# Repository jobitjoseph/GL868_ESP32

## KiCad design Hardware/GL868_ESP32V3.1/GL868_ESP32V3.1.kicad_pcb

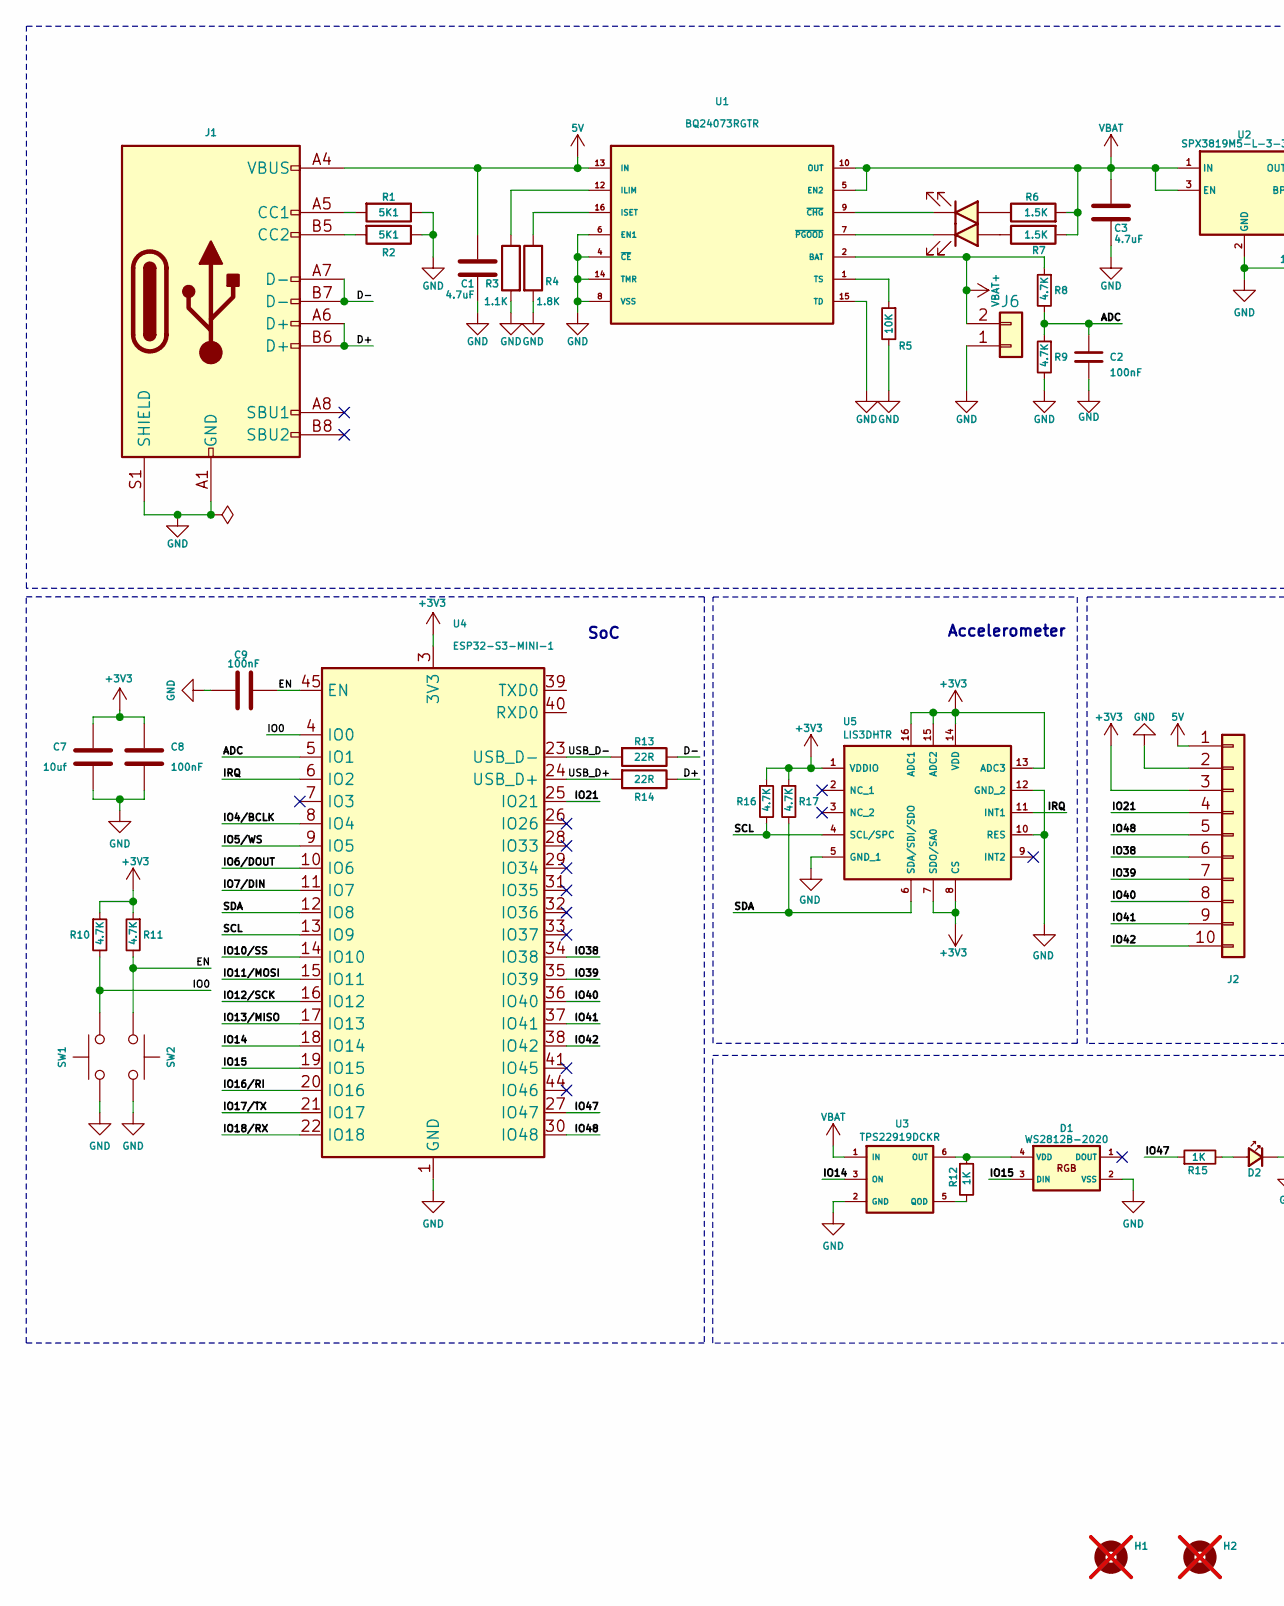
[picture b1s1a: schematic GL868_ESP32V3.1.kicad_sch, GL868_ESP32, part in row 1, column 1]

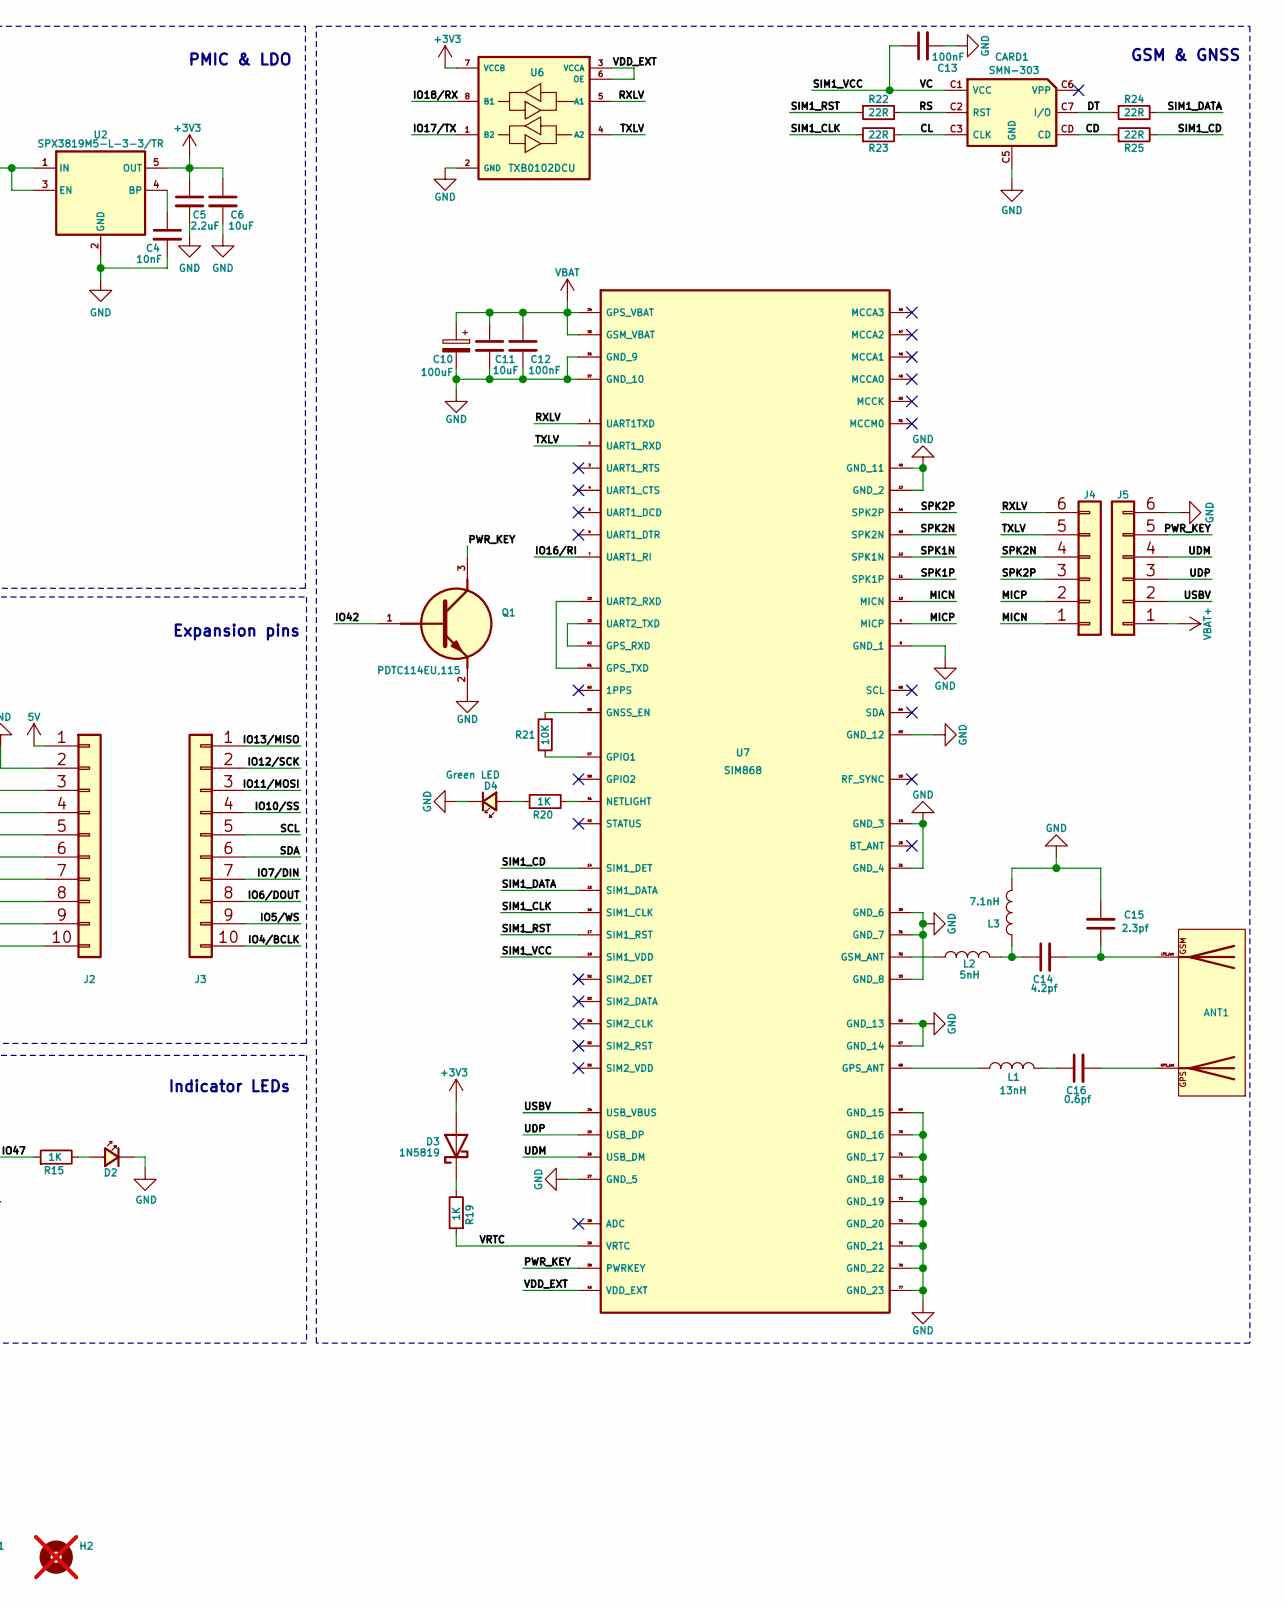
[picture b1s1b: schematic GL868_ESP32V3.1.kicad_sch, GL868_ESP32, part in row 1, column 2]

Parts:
ANT1: ANT; GL868_Combo_ANT
C1, C3: 4.7uF; C_0402_1005Metric; LCSC Part # C23733
C2, C8, C9, C12, C13: 100nF; C_0402_1005Metric; LCSC Part # C307331
C4: 10nF; C_0402_1005Metric; LCSC Part # C15195
C5: 2.2uF; C_0402_1005Metric; LCSC Part # C12530
C6, C11: 10uF; C_0402_1005Metric; LCSC Part # C15525
C7: 10uf; C_0402_1005Metric; LCSC Part # C15525
C10: 100uF; CP_EIA-3528-15_AVX-H; LCSC Part # C16133
C14: 4.2pf; C_0402_1005Metric; LCSC Part # C1855356
C15: 2.3pf; C_0402_1005Metric; LCSC Part # C2190124
C16: 0.6pf; C_0402_1005Metric; LCSC Part # C426333
CARD1: SMN-303; SIM-SMD_SMN-303; Manufacturer Part SMN-303; LCSC Part # C266888
D1: WS2812B-2020; LED_WS2812B-2020_PLCC4_2.0x2.0mm; LCSC Part # C5349955
D2, D4: Green LED; LED_0603_1608Metric; LCSC Part # C965804
D3: 1N5819; D_SOD-523; LCSC Part # C5185918
H1, H2: MountingHole; MountingHole_2.2mm_M2_DIN965; not fitted
J1: USB_C_Receptacle_USB2.0; USB_C_Receptacle_HRO_TYPE-C-31-M-12; LCSC Part # C2765186
J2, J3: Conn_01x10; PinHeader_1x10_P2.54mm_Vertical
J4, J5: Conn_01x06; PinHeader_1x06_P2.54mm_Vertical
J6: Conn_01x02; CONN-SMD_2P-P2.50_HCTL_HC-XH-2ALT; LCSC Part # C7429680
L1: 13nH; L_0402_1005Metric; LCSC Part # C2991840
L2: 5nH; L_0402_1005Metric
L3: 7.1nH; L_0402_1005Metric
LED1: Red LED; LED_0603_1608Metric; LCSC Part # C2286
LED2: Blue LED; LED_0603_1608Metric; LCSC Part # C965807
Q1: PDTC114EU,115; PDTC114EU115; LCSC Part # C135830
R1, R2: 5K1; R_0402_1005Metric; LCSC Part # C25905
R3: 1.1K; R_0402_1005Metric; LCSC Part # C174195
R4: 1.8K; R_0402_1005Metric; LCSC Part # C25867
R5, R21: 10K; R_0402_1005Metric; LCSC Part # C25744
R6, R7: 1.5K; R_0402_1005Metric; LCSC Part # C25867
R8, R9, R10, R11, R16, R17: 4.7K; R_0402_1005Metric; LCSC Part # C25900
R12, R15, R19, R20: 1K; R_0402_1005Metric; LCSC Part # C11702
R13, R14, R22, R23, R24, R25: 22R; R_0402_1005Metric; LCSC Part # C25092
SW1, SW2: SW_Push; Tactile 3x4x2mm TS-A010; LCSC Part # C720477
U1: BQ24073RGTR; IC_BQ24072RGTR; LCSC Part # C15220
U2: SPX3819M5-L-3-3/TR; SOT-23-5; LCSC Part # C9055
U3: TPS22919DCKR; SOT65P210X110-6N; LCSC Part # C2149796
U4: ESP32-S3-MINI-1; ESP32-S2-MINI-1; LCSC Part # C3013941
U5: LIS3DHTR; LCSC Part # C15134
U6: TXB0102DCU; VSSOP-8_2.3x2mm_P0.5mm; LCSC Part # C60709
U7: SIM868; LCSC Part # C39162023

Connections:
5V: C1.1, J1.A4 (VBUS), J1.A9 (VBUS), J1.B4 (VBUS), J1.B9 (VBUS), J2.1, U1.13 (IN)
+3V3: C5.1, C6.1, C7.1, C8.1, D3.2 (A), J2.3, R10.1, R11.1, R16.1, R17.1, U2.5 (OUT), U4.3 (3V3), U5.1 (VDDIO), U5.7 (SDO/SA0), U5.8 (CS), U5.13 (ADC3), U5.14 (VDD), U5.15 (ADC2), U5.16 (ADC1), U6.7 (VCCB)
/ADC: C2.1, R8.2, R9.1, U4.5 (IO1)
/CD: CARD1.CD, R25.1
/CL: CARD1.C3 (CLK), R23.2
/D+: J1.A6 (D+), J1.B6 (D+), R14.1
/D-: J1.A7 (D-), J1.B7 (D-), R13.1
/DT: CARD1.C7 (I/O), R24.1
/EN: C9.1, R11.2, SW2.1, U4.45 (EN)
/IO0: R10.2, SW1.2, U4.4 (IO0)
/IO4/BCLK: J3.10, U4.8 (IO4)
/IO5/WS: J3.9, U4.9 (IO5)
/IO6/DOUT: J3.8, U4.10 (IO6)
/IO7/DIN: J3.7, U4.11 (IO7)
/IO10/SS: J3.4, U4.14 (IO10)
/IO11/MOSI: J3.3, U4.15 (IO11)
/IO12/SCK: J3.2, U4.16 (IO12)
/IO13/MISO: J3.1, U4.17 (IO13)
/IO14: U3.3 (ON), U4.18 (IO14)
/IO15: D1.3 (DIN), U4.19 (IO15)
/IO16/RI: U4.20 (IO16), U7.7 (UART1_RI)
/IO17/TX: U4.21 (IO17), U6.1 (B2)
/IO18/RX: U4.22 (IO18), U6.8 (B1)
/IO21: J2.4, U4.25 (IO21)
/IO38: J2.6, U4.34 (IO38)
/IO39: J2.7, U4.35 (IO39)
/IO40: J2.8, U4.36 (IO40)
/IO41: J2.9, U4.37 (IO41)
/IO42: J2.10, Q1.1 (B), U4.38 (IO42)
/IO47: R15.1, U4.27 (IO47)
/IO48: J2.5, U4.30 (IO48)
/IRQ: U4.6 (IO2), U5.11 (INT1)
/MICN: J4.1, U7.10 (MICN)
/MICP: J4.2, U7.9 (MICP)
/PWR_KEY: J5.5, Q1.3 (C), U7.39 (PWRKEY)
/RS: CARD1.C2 (RST), R22.2
/RXLV: J4.6, U6.5 (A1), U7.1 (UART1TXD)
/SCL: J3.5, R16.2, U4.13 (IO9), U5.4 (SCL/SPC)
/SDA: J3.6, R17.2, U4.12 (IO8), U5.6 (SDA/SDI/SDO)
/SIM1_CD: R25.2, U7.14 (SIM1_DET)
/SIM1_CLK: R23.1, U7.16 (SIM1_CLK)
/SIM1_DATA: R24.2, U7.15 (SIM1_DATA)
/SIM1_RST: R22.1, U7.17 (SIM1_RST)
/SIM1_VCC: C13.1, CARD1.C1 (VCC), U7.18 (SIM1_VDD)
/SPK1N: U7.12 (SPK1N)
/SPK1P: U7.11 (SPK1P)
/SPK2N: J4.4, U7.43 (SPK2N)
/SPK2P: J4.3, U7.44 (SPK2P)
/TXLV: J4.5, U6.4 (A2), U7.2 (UART1_RXD)
/UDM: J5.4, U7.26 (USB_DM)
/UDP: J5.3, U7.25 (USB_DP)
/USBV: J5.2, U7.24 (USB_VBUS)
/USB_D+: R14.2, U4.24 (USB_D+)
/USB_D-: R13.2, U4.23 (USB_D-)
/VDD_EXT: U6.3 (VCCA), U6.6 (OE), U7.40 (VDD_EXT)
/VRTC: R19.1, U7.28 (VRTC)
GND: C1.2, C2.2, C3.2, C4.2, C5.2, C6.2, C7.2, C8.2, C9.2, C10.2, C11.2, C12.2, C13.2, C15.2, CARD1.8 (EP), CARD1.9 (EP), CARD1.10 (EP), CARD1.11 (EP), CARD1.C5 (GND), D1.2 (VSS), D2.1 (K), D4.1 (K), J1.A1 (GND), J1.A12 (GND), J1.B1 (GND), J1.B12 (GND), J1.S1 (SHIELD), J2.2, J5.6, J6.1, L3.2, Q1.2 (E), R1.1, R2.1, R3.2, R4.2, R5.2, R9.2, SW1.1, SW2.2, U1.4 (~CE), U1.6 (EN1), U1.8 (VSS), U1.14 (TMR), U1.15 (TD), U1.17 (EXP), U2.2 (GND), U3.2 (GND), U4.1 (GND), U4.2 (GND), U4.42 (GND), U4.43 (GND), U4.46 (GND), U4.47 (GND), U4.48 (GND), U4.49 (GND), U4.50 (GND), U4.51 (GND), U4.52 (GND), U4.53 (GND), U4.54 (GND), U4.55 (GND), U4.56 (GND), U4.57 (GND), U4.58 (GND), U4.59 (GND), U4.60 (GND), U4.61 (GND), U4.62 (GND), U4.63 (GND), U4.64 (GND), U4.65 (GND), U5.5 (GND_1), U5.10 (RES), U5.12 (GND_2), U6.2 (GND), U7.8 (GND_1), U7.13 (GND_2), U7.19 (GND_3), U7.21 (GND_4), U7.27 (GND_5), U7.30 (GND_6), U7.31 (GND_7), U7.33 (GND_8), U7.36 (GND_9), U7.37 (GND_10), U7.45 (GND_11), U7.63 (GND_12), U7.66 (GND_13), U7.67 (GND_14), U7.69 (GND_15), U7.70 (GND_16), U7.71 (GND_17), U7.72 (GND_18), U7.73 (GND_19), U7.74 (GND_20), U7.75 (GND_21), U7.76 (GND_22), U7.77 (GND_23)
unnamed: ANT1.GPS_Ant, C16.2
unnamed: ANT1.LTE_Ant, C14.2, C15.1
unnamed: C14.1, L2.2, L3.1
unnamed: C16.1, L1.2
unnamed: D1.4 (VDD), R12.1, U3.6 (OUT)
unnamed: D2.2 (A), R15.2
unnamed: D3.1 (K), R19.2
unnamed: D4.2 (A), R20.1
unnamed: J1.A5 (CC1), R1.2
unnamed: J1.B5 (CC2), R2.2
unnamed: LED1.2 (A), R6.1
unnamed: LED1.1 (K), U1.9 (~CHG)
unnamed: LED2.2 (A), R7.1
unnamed: LED2.1 (K), U1.7 (~PGOOD)
unnamed: R3.1, U1.12 (ILIM)
unnamed: R4.1, U1.16 (ISET)
unnamed: R5.1, U1.1 (TS)
unnamed: C4.1, U2.4 (BP)
unnamed: R12.2, U3.5 (QOD)
unnamed: R21.1, U7.59 (GNSS_EN)
unnamed: R21.2, U7.57 (GPIO1)
unnamed: L1.1, U7.68 (GPS_ANT)
unnamed: U7.22 (UART2_TXD), U7.62 (GPS_RXD)
unnamed: U7.23 (UART2_RXD), U7.61 (GPS_TXD)
unnamed: L2.1, U7.32 (GSM_ANT)
unnamed: R20.2, U7.41 (NETLIGHT)
VBAT: C3.1, C10.1, C11.1, C12.1, R6.2, R7.2, U1.5 (EN2), U1.10 (OUT), U1.11 (OUT), U2.1 (IN), U2.3 (EN), U3.1 (IN), U7.34 (GPS_VBAT), U7.35 (GSM_VBAT)
VBAT+: J5.1, J6.2, R8.1, U1.2 (BAT), U1.3 (BAT)

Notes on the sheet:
PMIC & LDO
Indicator LEDs
Accelerometer
Expansion pins
SoC
GSM & GNSS

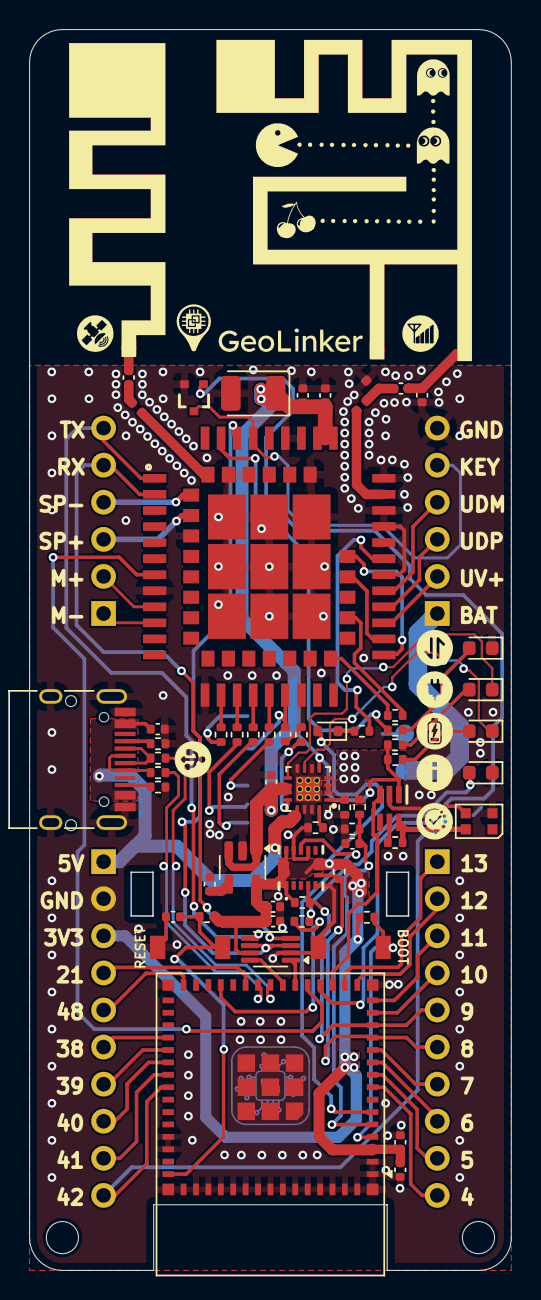
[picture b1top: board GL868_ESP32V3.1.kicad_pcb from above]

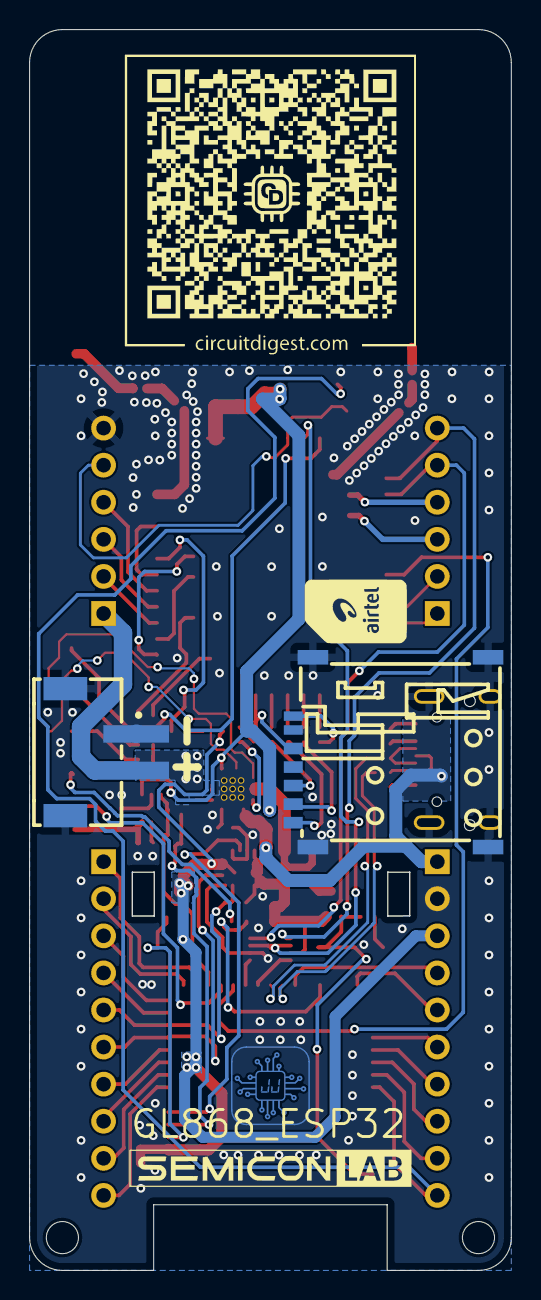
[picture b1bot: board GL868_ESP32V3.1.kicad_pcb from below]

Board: 2 copper layers, 33.0 x 85.0 mm, 69 parts (6 on the bottom side), 83 nets.

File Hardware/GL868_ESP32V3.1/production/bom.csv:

Designator,Footprint,Quantity,Value,LCSC Part #
"C1, C3",0402,2,4.7uF,C23733
C10,CP_EIA-3528-15_AVX-H,1,100uF,C16133
"C11, C6, C7",0402,3,10uF,C15525
"C12, C13, C2, C8, C9",0402,5,100nF,C307331
C14,0402,1,4.2pf,C1855356
C15,0402,1,2.3pf,C2190124
C16,0402,1,0.6pf,C426333
C4,0402,1,10nF,C15195
C5,0402,1,2.2uF,C12530
CARD1,SIM-SMD_SMN-303,1,SMN-303,C266888
D1,LED_WS2812B-2020_PLCC4_2.0x2.0mm,1,WS2812B-2020,C5349955
"D2, D4",0603,2,Green LED,C965804
D3,D_SOD-523,1,1N5819,C5185918
J1,USB_C_Receptacle_HRO_TYPE-C-31-M-12,1,USB_C_Receptacle_USB2.0,C2765186
J6,CONN-SMD_2P-P2.50_HCTL_HC-XH-2ALT,1,Conn_01x02,C7429680
L1,0402,1,13nH, C2991840
L2,0402,1,5nH,
L3,0402,1,7.1nH,
LED1,0603,1,Red LED,C2286
LED2,0603,1,Blue LED,C965807
Q1,PDTC114EU115,1,"PDTC114EU,115",C135830
"R1, R2",0402,2,5K1,C25905
"R10, R11, R16, R17, R8, R9",0402,6,4.7K,C25900
"R12, R15, R19, R20",0402,4,1K,C11702
"R13, R14, R22, R23, R24, R25",0402,6,22R,C25092
"R21, R5",0402,2,10K,C25744
R3,0402,1,1.1K,C174195
R4,0402,1,1.8K,C25867
"R6, R7",0402,2,1.5K,C25867
"SW1, SW2",Tactile 3x4x2mm TS-A010,2,SW_Push,C720477
U1,IC_BQ24072RGTR,1,BQ24073RGTR,C15220
U2,SOT-23-5,1,SPX3819M5-L-3-3/TR,C9055
U3,SOT65P210X110-6N,1,TPS22919DCKR,C2149796
U4,ESP32-S2-MINI-1,1,ESP32-S3-MINI-1,C3013941
U5,LIS3DHTR,1,LIS3DHTR,C15134
U6,VSSOP-8_2.3x2mm_P0.5mm,1,TXB0102DCU,C60709
U7,SIM868,1,SIM868,C39162023

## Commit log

2026-03-16 Add export-ignore attribute to .gitattributes
2026-03-17 feat: Continuous motion check before sleep, 30mg threshold, v1.0.3
